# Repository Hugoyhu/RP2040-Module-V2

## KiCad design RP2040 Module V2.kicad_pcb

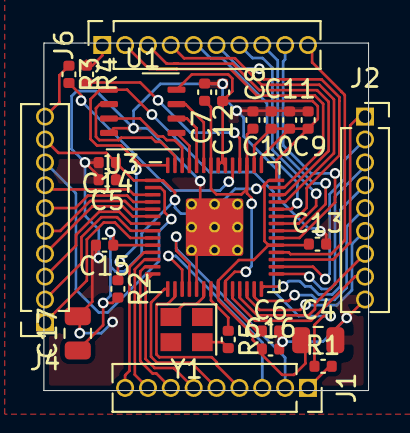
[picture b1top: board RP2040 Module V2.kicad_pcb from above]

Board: 2 copper layers, 18.0 x 19.3 mm, 26 parts (0 on the bottom side), 50 nets.

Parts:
C4, C17: 10u; C_0805_2012Metric
C5, C6, C7, C9, C11, C12, C13, C14, C15, C16: 100n; C_0402_1005Metric
C8, C10: 1u; C_0402_1005Metric
J1, J2: Conn_01x09; PinSocket_1x09_P1.27mm_Vertical
J4, J6: Conn_01x10; PinSocket_1x10_P1.27mm_Vertical
R1, R5: 1k; C_0402_1005Metric
R2: DNF; C_0402_1005Metric
R3, R4: 27; C_0402_1005Metric
U1: W25Q16JVUXIQ; HVSON-8-1EP_4x4mm_P0.8mm_EP2.2x3.1mm
U3: RP2040; RP2040-QFN-56
Y1: Crystal_GND24; Crystal_SMD_2520-4Pin_2.5x2.0mm

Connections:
+1V1: C6.1, C7.1, C8.1, U3.23, U3.45, U3.50
+3V3: C4.1, C5.1, C9.1, C10.1, C11.1, C12.1, C13.1, C14.1, C15.1, C16.1, C17.1, J4.9, R2.2, U1.8, U3.1, U3.10, U3.22, U3.33, U3.42, U3.43, U3.44, U3.48, U3.49
/GPIO0: J4.8, U3.2
/GPIO1: J4.7, U3.3
/GPIO2: J4.6, U3.4
/GPIO3: J4.5, U3.5
/GPIO4: J4.4, U3.6
/GPIO5: J4.3, U3.7
/GPIO6: J4.2, U3.8
/GPIO7: J4.1, U3.9
/GPIO8: J1.9, U3.11
/GPIO9: J1.8, U3.12
/GPIO10: J1.7, U3.13
/GPIO11: J1.6, U3.14
/GPIO12: J1.5, U3.15
/GPIO13: J1.4, U3.16
/GPIO14: J1.3, U3.17
/GPIO15: J1.2, U3.18
/GPIO16: J2.5, U3.27
/GPIO17: J2.4, U3.28
/GPIO18: J2.3, U3.29
/GPIO19: J2.2, U3.30
/GPIO20: J2.1, U3.31
/GPIO21: J6.10, U3.32
/GPIO22: J6.9, U3.34
/GPIO23: J6.8, U3.35
/GPIO24: J6.7, U3.36
/GPIO25: J6.6, U3.37
/GPIO26_ADC0: J6.5, U3.38
/GPIO27_ADC1: J6.4, U3.39
/GPIO28_ADC2: J6.3, U3.40
/GPIO29_ADC3: J6.2, U3.41
/QSPI_SCLK: U1.6, U3.52
/QSPI_SD0: U1.5, U3.53
/QSPI_SD1: U1.2, U3.55
/QSPI_SD2: U1.3, U3.54
/QSPI_SD3: U1.7, U3.51
/QSPI_SS: R1.1, R2.1, U1.1, U3.56
/RUN: J2.6, U3.26
/SWCLK: J2.8, U3.24
/SWD: J2.7, U3.25
/USB_D+: J4.10, R3.1
/USB_D-: J6.1, R4.1
/XIN: U3.20, Y1.3
/XOUT: R5.1, U3.21
/~USB_BOOT: J1.1, R1.2
GND: C4.2, C5.2, C6.2, C7.2, C8.2, C9.2, C10.2, C11.2, C12.2, C13.2, C14.2, C15.2, C16.2, C17.2, J2.9, U1.4, U3.19, U3.57
unnamed: R5.2, Y1.1
unnamed: R3.2, U3.47
unnamed: R4.2, U3.46

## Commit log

2021-04-29 this should fix it
    LOOK MY BRAIN ISN'T WORKING
    fixed some track issues because I was stupid and deleted some caps
